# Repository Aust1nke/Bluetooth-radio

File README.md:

# Bluetooth-radio
I designed a radio with bluetooth capability and also being able to be controlled from a phone.

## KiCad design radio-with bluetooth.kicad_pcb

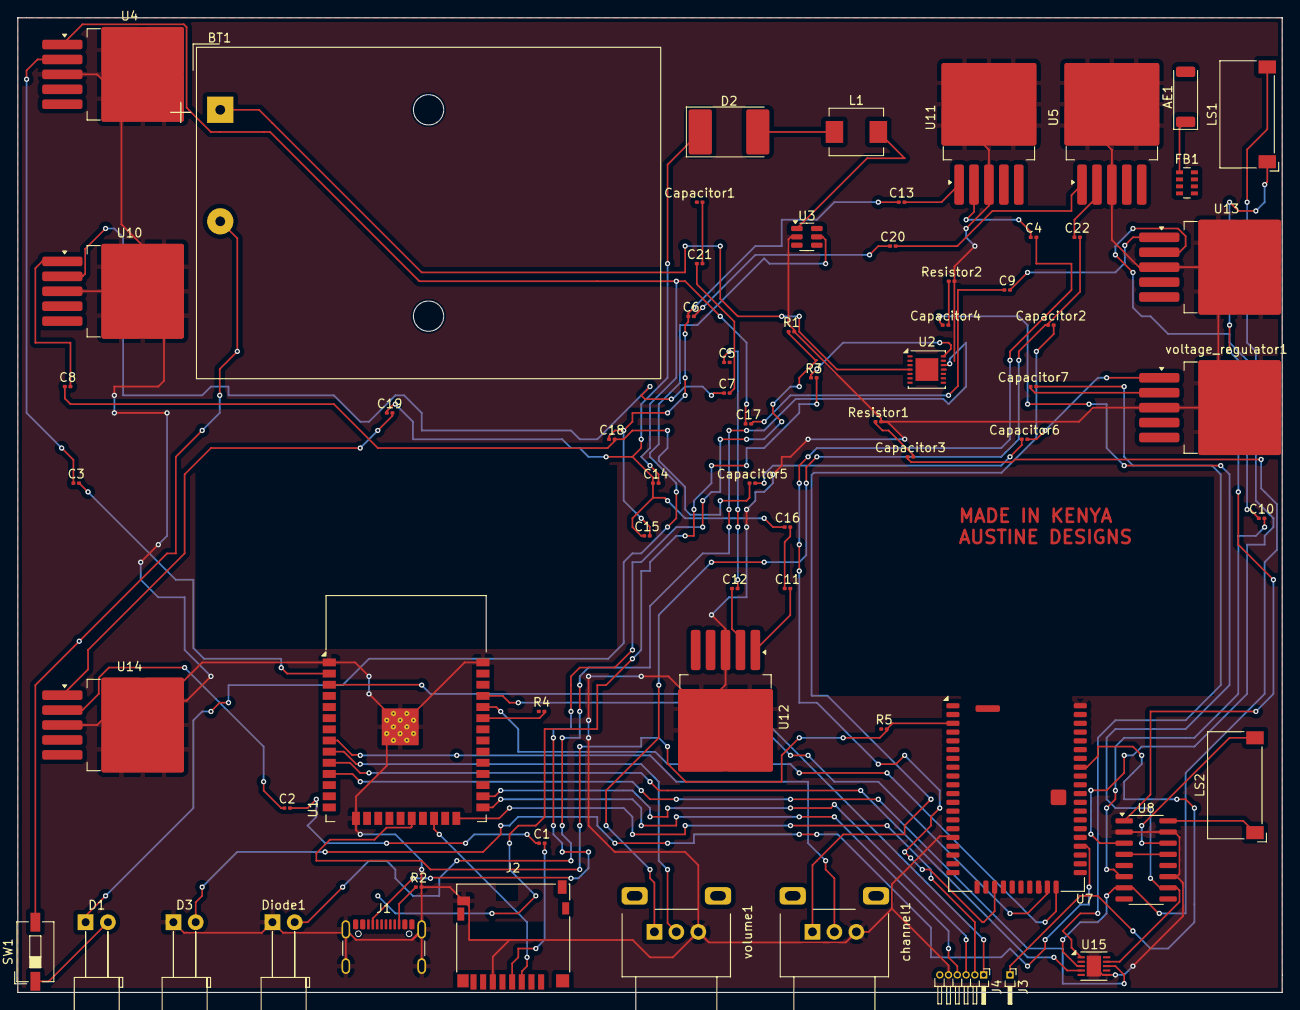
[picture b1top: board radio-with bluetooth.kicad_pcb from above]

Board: 2 copper layers, 144.0 x 111.0 mm, 67 parts (0 on the bottom side), 71 nets.

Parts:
AE1: Antenna; Johanson_2450AT43F0100
BT1: Battery; BatteryHolder_Keystone_2479_3xAAA
C1, C21: 10uF; C_0201_0603Metric
C2, C3, C4, C7, C8, C9, C10, C11, C12, C13, C14, C20, C22: 1000uF; C_0201_0603Metric
C5: 100uF; C_0201_0603Metric
C6, C15, C16, C17, C18, C19: 100nF; C_0201_0603Metric
Capacitor1, Capacitor6, Capacitor7: 1000uF; C_0201_0603Metric
Capacitor2: 0.1uF; C_0201_0603Metric
Capacitor3, Capacitor4, Capacitor5: 100nF; C_0201_0603Metric
D1, D3: LED; LED_D5.0mm_Horizontal_O6.35mm_Z9.0mm
D2: D_Schottky; D_3220_8050Metric_Pad2.65x5.15mm_HandSolder
Diode1: LED; LED_D5.0mm_Horizontal_O6.35mm_Z9.0mm
FB1: FerriteBead; L_Taiyo-Yuden_BK_Array_1206_3216Metric
J1: USB_C_Receptacle_PowerOnly_6P; USB_C_Receptacle_GCT_USB4105-xx-A_16P_TopMnt_Horizontal
J2: Micro_SD_Card; microSD_HC_Hirose_DM3D-SF
J3: Conn_01x01_Pin; PinHeader_1x01_P1.00mm_Horizontal
J4: Conn_01x06_Pin; PinHeader_1x06_P1.00mm_Horizontal
L1: L; L_Neosid_SM-PIC0512H
LS1, LS2: Speaker; Speaker_CUI_CMR-1206S-67
R1, R2, R3: 10k; R_0201_0603Metric
R4, R5: 4.7k; R_0201_0603Metric
Resistor1, Resistor2: 1k; R_0201_0603Metric
SW1: on/off; SW_DIP_SPSTx01_Slide_6.7x4.1mm_W6.73mm_P2.54mm_LowProfile_J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
U1: ESP32-WROOM-32
U2: LP3947; WSON-14-1EP_4.0x4.0mm_P0.5mm_EP2.6x2.6mm
U3: MT3608; SOT-23-6
U4, U5, U10, U11, U12, U13, U14: LM2576HVS-3.3; TO-263-5_TabPin3
U7: Microchip_BM83
U8: PAM8403D; SOP-16_3.9x9.9mm_P1.27mm
U15: ADG884xCP; LFCSP-WD-10-1EP_3x3mm_P0.5mm_EP1.64x2.38mm
channel1: R_Potentiometer_Small; Potentiometer_Alps_RK09L_Single_Horizontal
voltage_regulator1: LM2576HVS-3.3; TO-263-5_TabPin3
volume1: R_Potentiometer_Small; Potentiometer_Alps_RK09L_Single_Horizontal

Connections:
GND: D3.1 (K), Diode1.1 (K), J1.A12 (GND), J1.B12 (GND), J1.S1 (SHIELD), J2.6 (VSS), J2.9 (SHIELD), J4.5, R1.2, R2.2, Resistor1.2, Resistor2.2, U1.1 (GND), U1.15 (GND), U1.38 (GND), U1.39 (GND), U2.11 (GND), U3.2 (GND), U4.3 (GND), U5.3 (GND), U7.16 (GND), U7.50 (GND), U7.56 (GND), U7.57 (GND), U8.2 (PGND), U8.11 (GND), U8.15 (PGND), U10.3 (GND), U11.3 (GND), U12.3 (GND), U13.3 (GND), U14.3 (GND), U15.6 (GND), U15.11 (GND), channel1.3, voltage_regulator1.3 (GND), volume1.3
unnamed: AE1.1 (A), FB1.1
unnamed: BT1.1 (+), U2.4 (BATT)
unnamed: BT1.2 (-), SW1.2 (B)
unnamed: C1.1, C2.2
unnamed: C11.1, C16.2
unnamed: C5.1, C12.2
unnamed: C6.1, C13.1, C15.2, C18.1
unnamed: C9.1, C17.2
unnamed: C8.1, C18.2, Capacitor5.1
unnamed: C6.2, C20.1
unnamed: C7.2, C21.1
unnamed: C22.2, Capacitor2.1, volume1.1
unnamed: Capacitor2.2, channel1.1
unnamed: Capacitor3.2, Resistor1.1
unnamed: Capacitor4.2, Resistor2.1
unnamed: Capacitor5.2, Capacitor6.1
unnamed: D1.2 (A), SW1.1 (A)
unnamed: D1.1 (K), U3.5 (IN)
unnamed: D2.2 (A), L1.1
unnamed: C14.1, C15.1, C16.1, C19.1, D2.1 (K)
unnamed: D3.2 (A), U7.34 (LED2)
unnamed: Diode1.2 (A), U2.12 (CHG)
unnamed: J1.A5 (CC1), R1.1
unnamed: J1.B5 (CC2), R2.1
unnamed: J1.A9 (VBUS), J1.B9 (VBUS), R3.2
unnamed: J2.3 (CMD), U1.22 (SDI/SD1)
unnamed: C1.2, J2.4 (VDD)
unnamed: J3.1, U7.43 (~RST)
unnamed: J4.1, U1.3 (EN)
unnamed: J4.2, U1.24 (IO2)
unnamed: J4.3, U1.26 (IO4)
unnamed: J4.4, U1.25 (IO0)
unnamed: R4.2, U1.33 (IO21)
unnamed: U1.10 (IO25), U15.4 (IN1)
unnamed: U1.11 (IO26), U15.8 (IN2)
unnamed: U1.8 (IO32), channel1.2
unnamed: U1.9 (IO33), volume1.2
unnamed: U1.34 (RXD0/IO3), U7.30 (P8_5/UART_TXD)
unnamed: R5.2, U1.20 (SCK/CLK), U7.3 (SCLK1)
unnamed: U1.35 (TXD0/IO1), U7.29 (P8_6/UART_RXD)
unnamed: C3.2, U1.2 (VDD)
unnamed: R3.1, U2.14 (CHG_IN)
unnamed: L1.2, U3.1 (SW)
unnamed: C3.1, U4.2 (OUT)
unnamed: C14.2, C17.1, U4.1 (VIN)
unnamed: C22.1, U5.2 (OUT)
unnamed: C20.2, U5.1 (VIN)
unnamed: C21.2, Capacitor1.2
unnamed: C4.2, U7.23 (BAT_IN)
unnamed: LS1.1, U8.1 (LOUT+)
unnamed: LS1.2, U8.3 (LOUT-)
unnamed: U8.4 (PVDD), U8.13 (PVDD)
unnamed: LS2.1, U8.16 (ROUT+)
unnamed: LS2.2, U8.14 (ROUT-)
unnamed: C10.2, U8.6 (VDD)
unnamed: C7.1, U10.2 (OUT)
unnamed: C8.2, U10.1 (VIN)
unnamed: C4.1, U11.2 (OUT)
unnamed: C13.2, U11.1 (VIN)
unnamed: C12.1, U12.2 (OUT)
unnamed: C11.2, U12.1 (VIN)
unnamed: C10.1, U13.2 (OUT)
unnamed: C9.2, U13.1 (VIN)
unnamed: C2.1, U14.2 (OUT)
unnamed: C19.2, U14.1 (VIN)
unnamed: Capacitor3.1, U8.7 (INL), U15.3 (D1)
unnamed: Capacitor4.1, U8.10 (INR), U15.9 (D2)
unnamed: Capacitor7.2, U15.1 (VDD)
unnamed: Capacitor7.1, voltage_regulator1.2 (OUT)
unnamed: Capacitor6.2, voltage_regulator1.1 (VIN)

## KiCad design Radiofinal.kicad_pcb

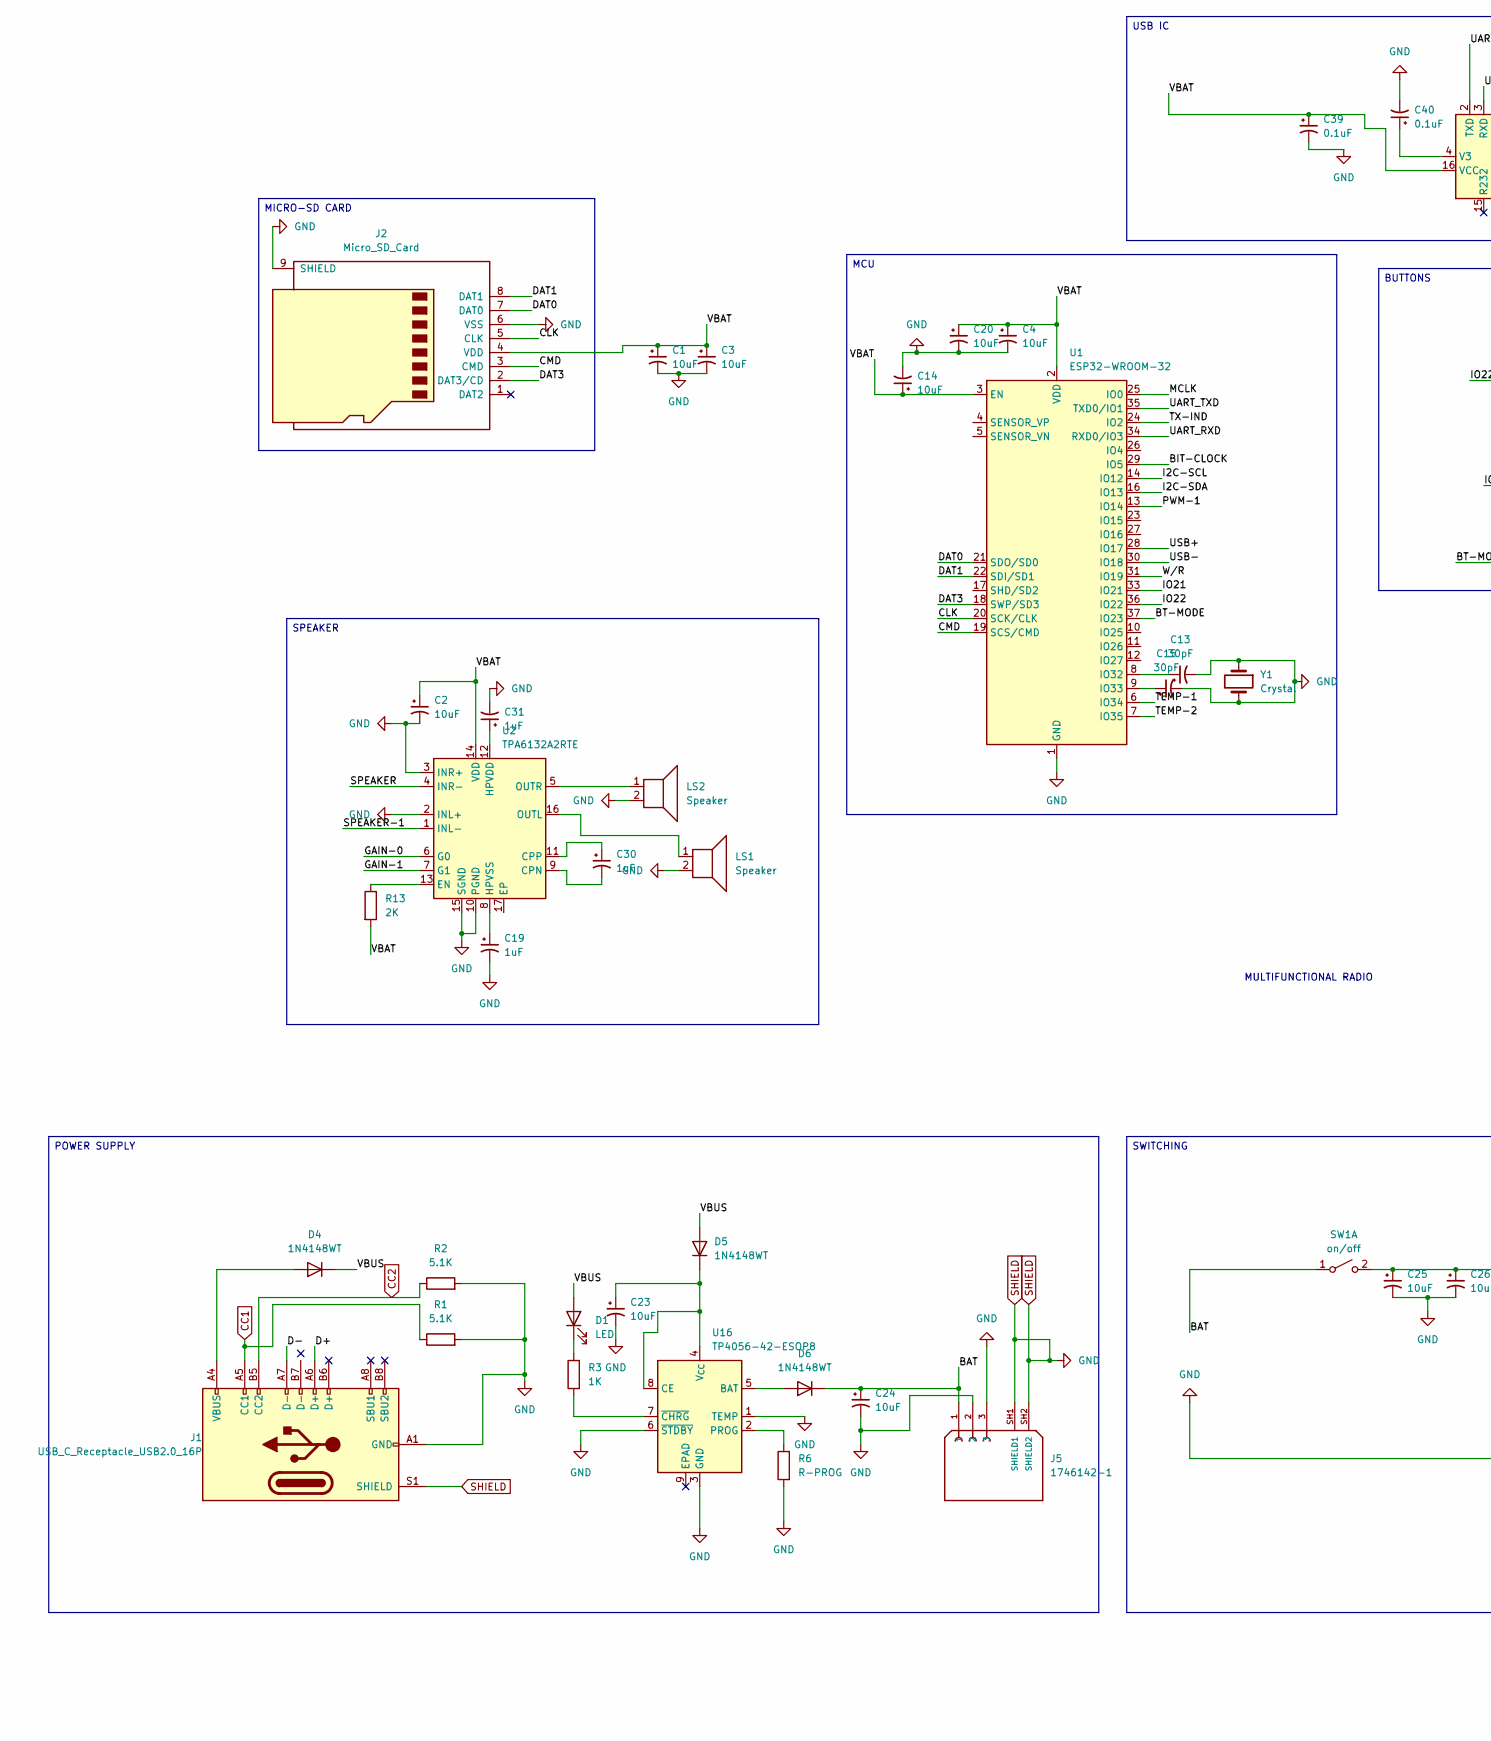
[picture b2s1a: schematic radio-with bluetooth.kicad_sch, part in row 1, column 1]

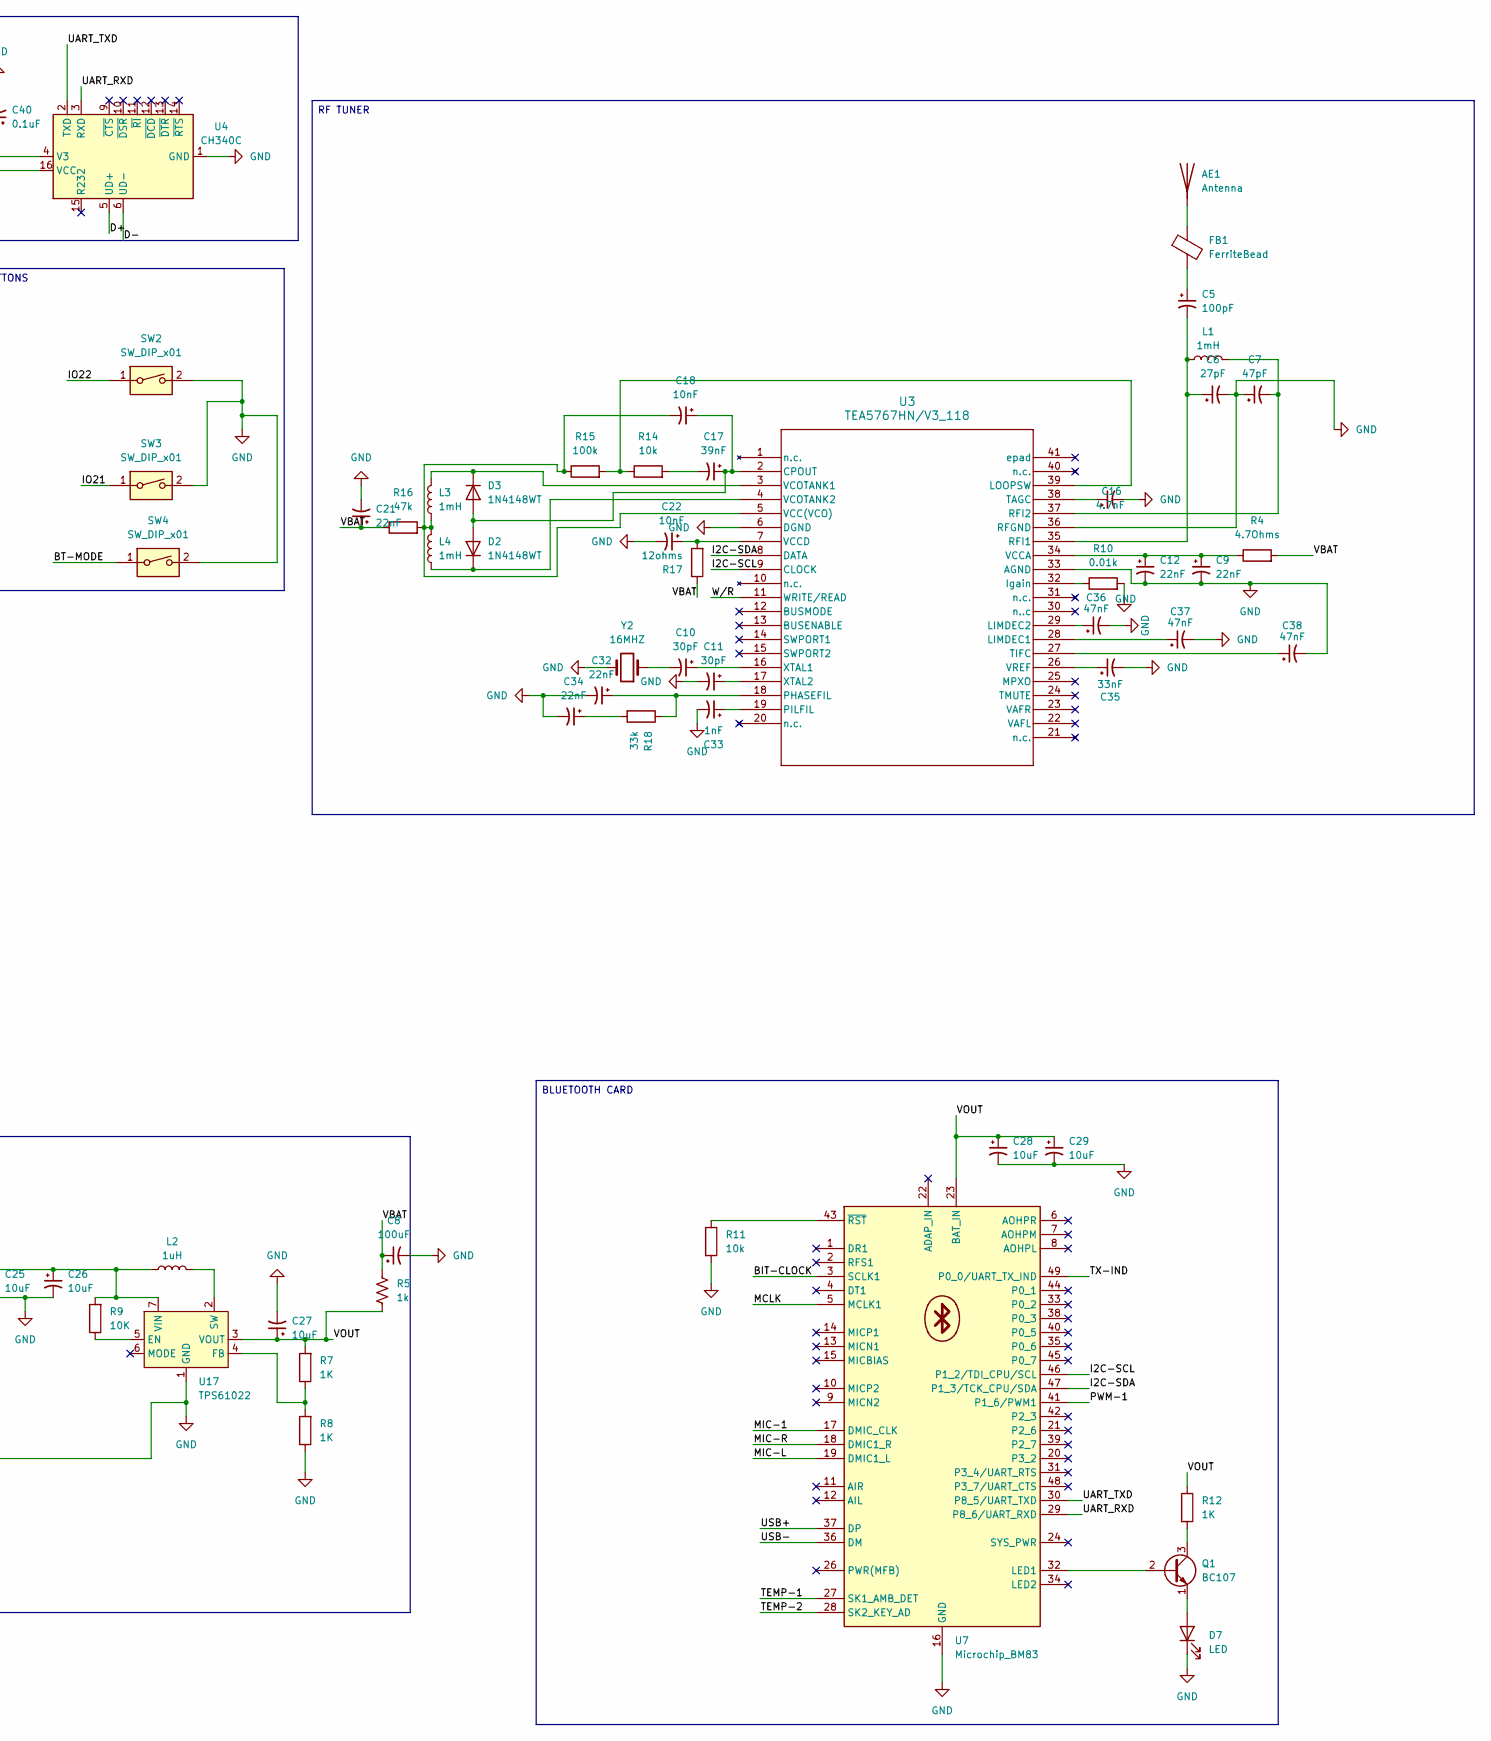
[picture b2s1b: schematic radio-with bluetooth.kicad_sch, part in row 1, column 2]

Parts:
AE1: Antenna; Johanson_2450AT43F0100
C1, C2, C3, C4, C14, C20, C23, C24, C25, C26, C27, C28, C29: 10uF; C_0201_0603Metric
C5: 100pF; C_0201_0603Metric
C6: 27pF; C_0201_0603Metric
C7: 47pF; C_0201_0603Metric
C8: 100uF; CP_Radial_D4.0mm_P1.50mm
C9, C12, C21, C32, C34: 22nF; C_0201_0603Metric
C10, C11, C13, C15: 30pF; C_0201_0603Metric
C16: 4.7nF; C_0201_0603Metric
C17: 39nF; C_0201_0603Metric
C18, C22: 10nF; C_0201_0603Metric
C19, C30, C31: 1uF; C_0201_0603Metric
C33: 1nF; C_0201_0603Metric
C35: 33nF; C_0201_0603Metric
C36, C37, C38: 47nF; C_0201_0603Metric
C39, C40: 0.1uF; C_0201_0603Metric
D1: LED; LED_0201_0603Metric
D2, D3, D4, D5, D6: 1N4148WT; D_SOD-523
D7: LED
FB1: FerriteBead; L_Taiyo-Yuden_BK_Array_1206_3216Metric
J1: USB_C_Receptacle_USB2.0_16P; USB_C_Receptacle_G-Switch_GT-USB-7010ASV
J2: Micro_SD_Card; microSD_HC_Hirose_DM3D-SF
J5: 1746142-1; TE_1746142-1; PARTREV 01
L1, L3, L4: 1mH; L_Radial_D6.0mm_P4.00mm
L2: 1uH; L_Neosid_SM-PIC0512H
LS1, LS2: Speaker; Speaker_CUI_CMR-1206S-67
Q1: BC107; TO-18-3
R1, R2: 5.1K; R_0201_0603Metric
R3, R7, R8, R12: 1K; R_0201_0603Metric
R4: 4.7Ohms; R_0201_0603Metric
R5: 1k; R_0201_0603Metric
R6: R-PROG; R_0201_0603Metric
R9: 10K; R_0201_0603Metric
R10: 0.01k; R_0201_0603Metric
R11, R14: 10k; R_0201_0603Metric
R13: 2K; R_0201_0603Metric
R15: 100k; R_0201_0603Metric
R16: 47k; R_0201_0603Metric
R17: 12ohms; R_0201_0603Metric
R18: 33k; R_0201_0603Metric
SW1: on/off; SW_DIP_SPSTx01_Slide_6.7x4.1mm_W6.73mm_P2.54mm_LowProfile_J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
SW2, SW3, SW4: SW_DIP_x01; SW_Tactile_SPST_Angled_PTS645Vx31-2LFS
U1: ESP32-WROOM-32
U2: TPA6132A2RTE; WQFN-16-1EP_3x3mm_P0.5mm_EP1.6x1.6mm_ThermalVias
U3: TEA5767HN/V3_118; HVQFN40_SOT618-1_6X6_NXP-M
U4: CH340C; SOIC-16_3.9x9.9mm_P1.27mm
U7: Microchip_BM83
U16: TP4056-42-ESOP8; SOIC-8-1EP_3.9x4.9mm_P1.27mm_EP2.41x3.3mm_ThermalVias
U17: TPS61022; Texas_RWU0007A_VQFN-7_2x2mm_P0.5mm
Y1: Crystal; Crystal_SMD_ECS_CSM3X-2Pin_7.6x4.1mm
Y2: 16MHZ; Crystal_SMD_ECS_CSM3X-2Pin_7.6x4.1mm

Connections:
/BAT: C24.1, D6.1 (K), J5.1, SW1.1 (A)
/BIT-CLOCK: U1.29 (IO5), U7.3 (SCLK1)
/BT-MODE: SW4.1, U1.37 (IO23)
/CLK: J2.5 (CLK), U1.20 (SCK/CLK)
/CMD: J2.3 (CMD), U1.19 (SCS/CMD)
/D+: J1.A6 (D+), U4.5 (UD+)
/D-: J1.A7 (D-), U4.6 (UD-)
/DAT0: J2.7 (DAT0), U1.21 (SDO/SD0)
/DAT1: J2.8 (DAT1), U1.22 (SDI/SD1)
/DAT3: J2.2 (DAT3/CD), U1.18 (SWP/SD3)
/GAIN-0: U2.6 (G0)
/GAIN-1: U2.7 (G1)
/I2C-SCL: U1.14 (IO12), U3.9 (CLOCK), U7.46 (P1_2/TDI_CPU/SCL)
/I2C-SDA: U1.16 (IO13), U3.8 (DATA), U7.47 (P1_3/TCK_CPU/SDA)
/IO21: SW3.1, U1.33 (IO21)
/IO22: SW2.1, U1.36 (IO22)
/MCLK: U1.25 (IO0), U7.5 (MCLK1)
/MIC-1: U7.17 (DMIC_CLK)
/MIC-L: U7.19 (DMIC1_L)
/MIC-R: U7.18 (DMIC1_R)
/PWM-1: U1.13 (IO14), U7.41 (P1_6/PWM1)
/SPEAKER: U2.4 (INR-)
/SPEAKER-1: U2.1 (INL-)
/TEMP-1: U1.6 (IO34), U7.27 (SK1_AMB_DET)
/TEMP-2: U1.7 (IO35), U7.28 (SK2_KEY_AD)
/TX-IND: U1.24 (IO2), U7.49 (P0_0/UART_TX_IND)
/UART_RXD: U1.34 (RXD0/IO3), U4.3 (RXD), U7.29 (P8_6/UART_RXD)
/UART_TXD: U1.35 (TXD0/IO1), U4.2 (TXD), U7.30 (P8_5/UART_TXD)
/USB+: U1.28 (IO17), U7.37 (DP)
/USB-: U1.30 (IO18), U7.36 (DM)
/VBAT: C1.1, C2.1, C3.1, C4.1, C8.1, C14.1, C20.1, C21.1, C39.1, J2.4 (VDD), R4.2, R5.1, R13.2, R16.1, R17.1, U1.2 (VDD), U1.3 (EN), U2.14 (VDD), U4.16 (VCC)
/VBUS: D1.2 (A), D4.1 (K), D5.2 (A)
/VOUT: C27.1, C28.1, C29.1, R5.2, R7.2, R12.1, U7.23 (BAT_IN), U17.3 (VOUT)
/W/R: U1.31 (IO19), U3.11 (WRITE/READ)
CC1: J1.A5 (CC1), R1.1
CC2: J1.B5 (CC2), R2.1
unnamed: AE1.1 (A), FB1.1
unnamed: C5.1, FB1.2
unnamed: C10.2, Y2.1
unnamed: C17.2, R14.2
unnamed: C34.1, R18.2
unnamed: D1.1 (K), R3.2
unnamed: C17.1, C18.1, D2.2 (A), D3.2 (A), U3.2 (CPOUT)
unnamed: D2.1 (K), L4.1, U3.4 (VCOTANK2)
unnamed: D3.1 (K), L3.2, U3.3 (VCOTANK1)
unnamed: D4.2 (A), J1.A4 (VBUS), J1.A9 (VBUS), J1.B4 (VBUS), J1.B9 (VBUS)
unnamed: C23.1, D5.1 (K), U16.4 (V_{CC}), U16.8 (CE)
unnamed: D6.2 (A), U16.5 (BAT)
unnamed: D7.2 (A), Q1.1 (E)
unnamed: Q1.2 (B), U7.32 (LED1)
unnamed: Q1.3 (C), R12.2
unnamed: C25.1, C26.1, L2.1, R9.2, SW1.2 (B), U17.7 (VIN)
unnamed: C13.1, U1.8 (IO32)
unnamed: C15.1, U1.9 (IO33)
unnamed: C30.2, U2.9 (CPN)
unnamed: C30.1, U2.11 (CPP)
unnamed: R13.1, U2.13 (EN)
unnamed: C31.1, U2.12 (HPVDD)
unnamed: C19.1, U2.8 (HPVSS)
unnamed: LS1.1, U2.16 (OUTL)
unnamed: LS2.1, U2.5 (OUTR)
unnamed: R10.1, U3.32 (Igain)
unnamed: C37.1, U3.28 (LIMDEC1)
unnamed: C36.1, U3.29 (LIMDEC2)
unnamed: R14.1, R15.2, U3.39 (LOOPSW)
unnamed: C32.1, R18.1, U3.18 (PHASEFIL)
unnamed: C33.1, U3.19 (PILFIL)
unnamed: C5.2, C6.1, L1.1, U3.35 (RFI1)
unnamed: C7.2, L1.2, U3.37 (RFI2)
unnamed: C16.1, U3.38 (TAGC)
unnamed: C38.1, U3.27 (TIFC)
unnamed: C18.2, L3.1, L4.2, R15.1, R16.2, U3.5 (VCC(VCO))
unnamed: C9.1, C12.1, R4.1, U3.34 (VCCA)
unnamed: C22.1, R17.2, U3.7 (VCCD)
unnamed: C35.1, U3.26 (VREF)
unnamed: C10.1, U3.16 (XTAL1)
unnamed: C11.1, U3.17 (XTAL2)
unnamed: C40.1, U4.4 (V3)
unnamed: R11.1, U7.43 (~RST)
unnamed: R6.2, U16.2 (PROG)
unnamed: R3.1, U16.7 (~CHRG)
unnamed: R9.1, U17.5 (EN)
unnamed: R7.1, R8.2, U17.4 (FB)
unnamed: L2.2, U17.2 (SW)
SHIELD: C1.2, C2.2, C3.2, C4.2, C6.2, C7.1, C8.2, C9.2, C11.2, C12.2, C13.2, C14.2, C15.2, C16.2, C19.2, C20.2, C21.2, C22.2, C23.2, C24.2, C25.2, C26.2, C27.2, C28.2, C29.2, C31.2, C32.2, C33.2, C34.2, C35.2, C36.2, C37.2, C38.2, C39.2, C40.2, D7.1 (K), J1.A1 (GND), J1.A12 (GND), J1.B1 (GND), J1.B12 (GND), J1.S1 (SHIELD), J2.6 (VSS), J2.9 (SHIELD), J5.2, J5.3, J5.SH1 (SHIELD1), J5.SH2 (SHIELD2), LS1.2, LS2.2, R1.2, R2.2, R6.1, R8.1, R10.2, R11.2, SW2.2, SW3.2, SW4.2, U1.1 (GND), U1.15 (GND), U1.38 (GND), U1.39 (GND), U2.2 (INL+), U2.3 (INR+), U2.10 (PGND), U2.15 (SGND), U3.6 (DGND), U3.33 (AGND), U3.36 (RFGND), U4.1 (GND), U7.16 (GND), U7.50 (GND), U7.56 (GND), U7.57 (GND), U16.1 (TEMP), U16.3 (GND), U16.6 (~STDBY), U17.1 (GND), Y1.1, Y1.2, Y2.2

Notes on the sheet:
MULTIFUNCTIONAL RADIO
POWER SUPPLY
BLUETOOTH CARD
RF TUNER
BUTTONS
SWITCHING
MCU
MICRO-SD CARD
USB IC
SPEAKER

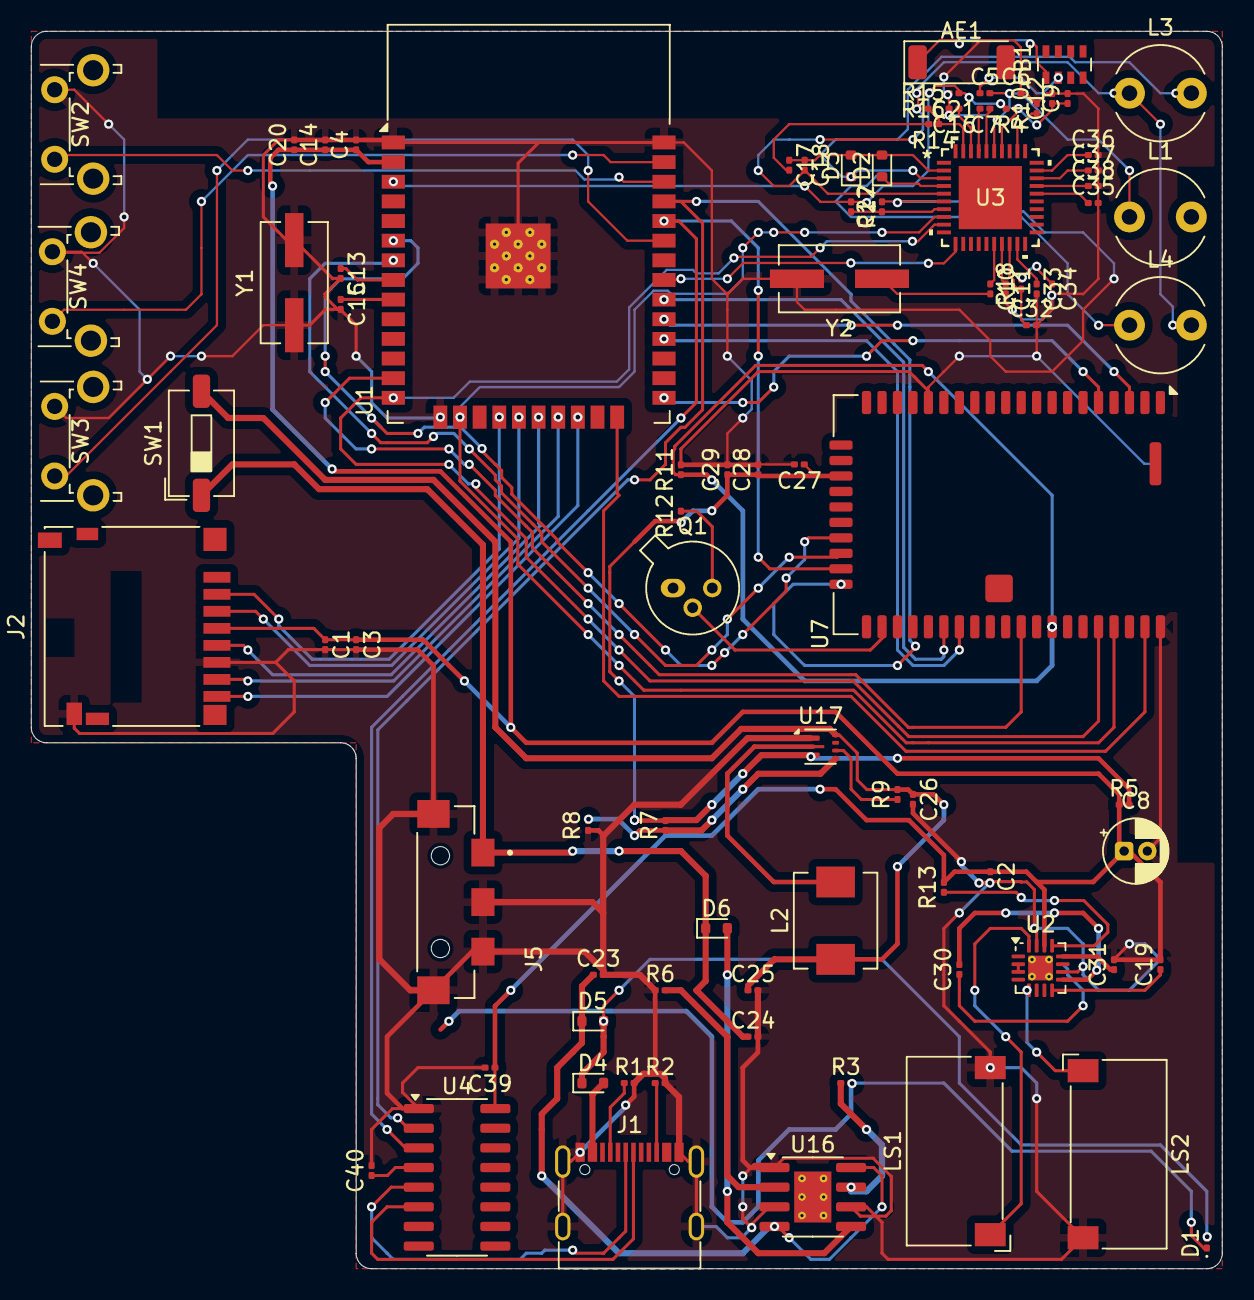
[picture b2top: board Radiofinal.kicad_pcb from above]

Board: 2 copper layers, 77.0 x 80.0 mm, 89 parts (0 on the bottom side), 77 nets.

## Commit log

2025-08-21 Add files via upload
    In this projects , I use esp32 microcontroller, with a dedicated bluetooth ic, also with multiple media player decorders programmable into the esp32, and also audio drivers to run the speakers on thi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
